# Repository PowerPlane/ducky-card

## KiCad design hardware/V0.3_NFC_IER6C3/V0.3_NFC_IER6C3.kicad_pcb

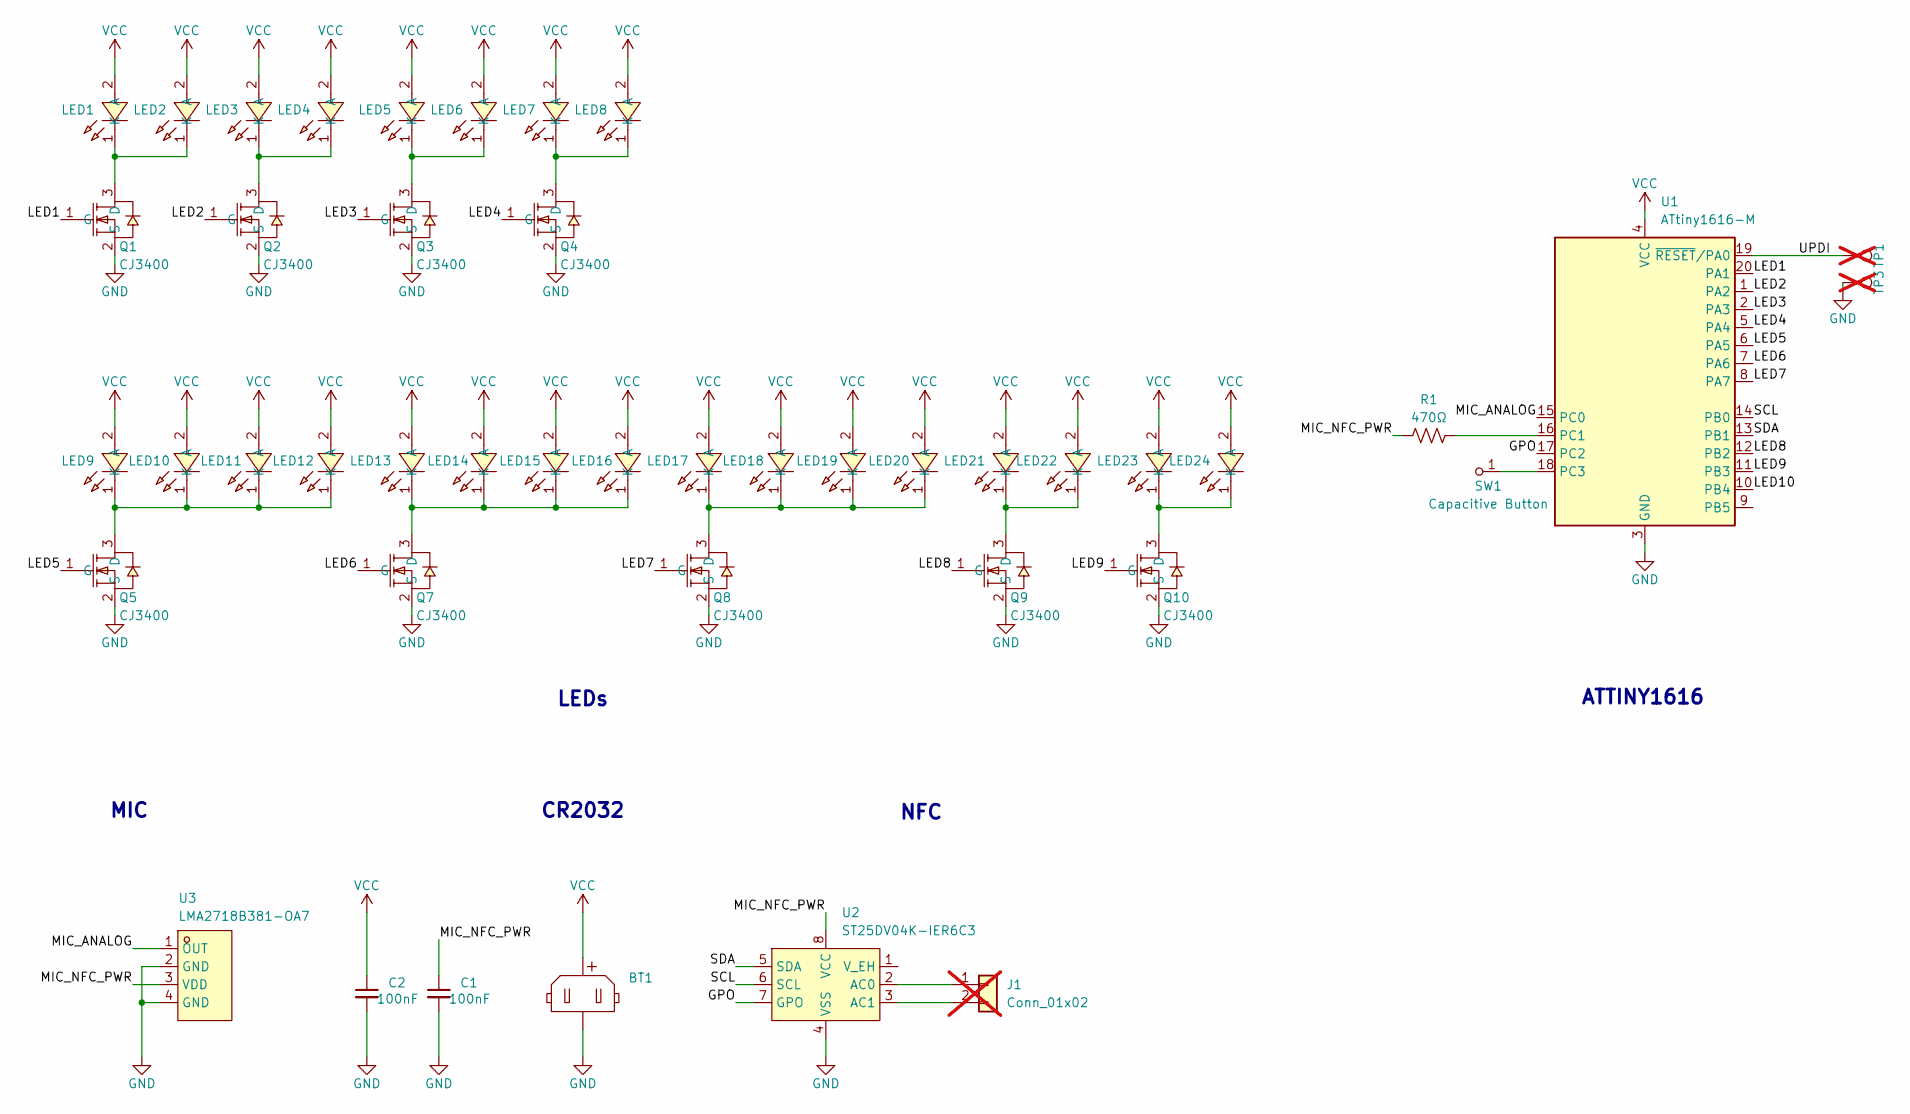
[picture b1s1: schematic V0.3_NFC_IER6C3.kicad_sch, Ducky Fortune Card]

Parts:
BT1: Battery-Holder_Coin-Cell_CR2032_Linx_BAT-HLD-001; BAT-SMD_MY-2032-08
C1, C2: 100nF; C_0805; Voltage 50V; Tolerance 100%; LCSC C28233
J1: Conn_01x02; NFC_Mini_Antenna_22x22_ST25DV04K; not fitted
LED1, LED2, LED3, LED4, LED5, LED6, LED7, LED8, LED9, LED10, LED11, LED12, LED13, LED14, LED15, LED16, LED17, LED18, LED19, LED20: XL-1606UYC; LED-SMD_L1.7-W1.1-RD_RED-SIDE; MPN XL-1606SURC; LCSC C965862
LED21, LED22: XL-1606UOC; LED-SMD_L1.7-W1.1-RD_RED-SIDE; MPN XL-1606SURC; LCSC C965861
LED23, LED24: XL-1606SURC; LED-SMD_L1.7-W1.1-RD_RED-SIDE; MPN XL-1606SURC; LCSC C965860
Q1, Q2, Q3, Q4, Q5, Q7, Q8, Q9, Q10: CJ3400; SOT23-3; MPN CJ3400; LCSC C19019
R1: 470Ω; R_0402; LCSC C25117
SW1: Capacitive Button; Ducky_Left_12mm_Overall
TP1, TP3: 1.0mm; DUCKY_ICON_2.54_Spacing; not fitted
U1: ATtiny1616-M; VQFN-20-1EP_3x3mm_P0.4mm_EP1.7x1.7mm; LCSC C507118
U2: ST25DV04K-IER6C3; DFN-8-1EP_3x2mm_P0.5mm_EP1.36x1.46mm; LCSC C2908287
U3: LMA2718B381-OA7; MIC-SMD_4P-L2.8-W1.9_LMA2718B381-OA7; MPN LMA2718B381-OA7; LCSC Part C5373222

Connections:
/GPO: U1.17 (PC2), U2.7 (GPO)
/LED1: Q1.1 (G), U1.20 (PA1)
/LED2: Q2.1 (G), U1.1 (PA2)
/LED3: Q3.1 (G), U1.2 (PA3)
/LED4: Q4.1 (G), U1.5 (PA4)
/LED5: Q5.1 (G), U1.6 (PA5)
/LED6: Q7.1 (G), U1.7 (PA6)
/LED7: Q8.1 (G), U1.8 (PA7)
/LED8: Q9.1 (G), U1.12 (PB2)
/LED9: Q10.1 (G), U1.11 (PB3)
/LED10: U1.10 (PB4)
/MIC_ANALOG: U1.15 (PC0), U3.1 (OUT)
/MIC_NFC_PWR: C1.1, R1.2, U2.8 (VCC), U3.3 (VDD)
/SCL: U1.14 (PB0), U2.6 (SCL)
/SDA: U1.13 (PB1), U2.5 (SDA)
/UPDI: TP1.1 (1_1), U1.19 (~RESET/PA0)
GND: BT1.2 (-), C1.2, C2.2, Q1.2 (S), Q2.2 (S), Q3.2 (S), Q4.2 (S), Q5.2 (S), Q7.2 (S), Q8.2 (S), Q9.2 (S), Q10.2 (S), TP3.1 (1_1), U1.3 (GND), U1.21 (GND), U2.4 (VSS), U3.2 (GND), U3.4 (GND)
unnamed: J1.1, U2.2 (AC0)
unnamed: J1.2, U2.3 (AC1)
unnamed: LED1.1 (K), LED2.1 (K), Q1.3 (D)
unnamed: LED3.1 (K), LED4.1 (K), Q2.3 (D)
unnamed: LED5.1 (K), LED6.1 (K), Q3.3 (D)
unnamed: LED7.1 (K), LED8.1 (K), Q4.3 (D)
unnamed: LED9.1 (K), LED10.1 (K), LED11.1 (K), LED12.1 (K), Q5.3 (D)
unnamed: LED13.1 (K), LED14.1 (K), LED15.1 (K), LED16.1 (K), Q7.3 (D)
unnamed: LED17.1 (K), LED18.1 (K), LED19.1 (K), LED20.1 (K), Q8.3 (D)
unnamed: LED21.1 (K), LED22.1 (K), Q9.3 (D)
unnamed: LED23.1 (K), LED24.1 (K), Q10.3 (D)
unnamed: SW1.1 (A_1), U1.18 (PC3)
unnamed: R1.1, U1.16 (PC1)
VCC: BT1.1 (+), C2.1, LED1.2 (A), LED2.2 (A), LED3.2 (A), LED4.2 (A), LED5.2 (A), LED6.2 (A), LED7.2 (A), LED8.2 (A), LED9.2 (A), LED10.2 (A), LED11.2 (A), LED12.2 (A), LED13.2 (A), LED14.2 (A), LED15.2 (A), LED16.2 (A), LED17.2 (A), LED18.2 (A), LED19.2 (A), LED20.2 (A), LED21.2 (A), LED22.2 (A), LED23.2 (A), LED24.2 (A), U1.4 (VCC)

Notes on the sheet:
NFC
LEDs
CR2032
ATTINY1616
MIC

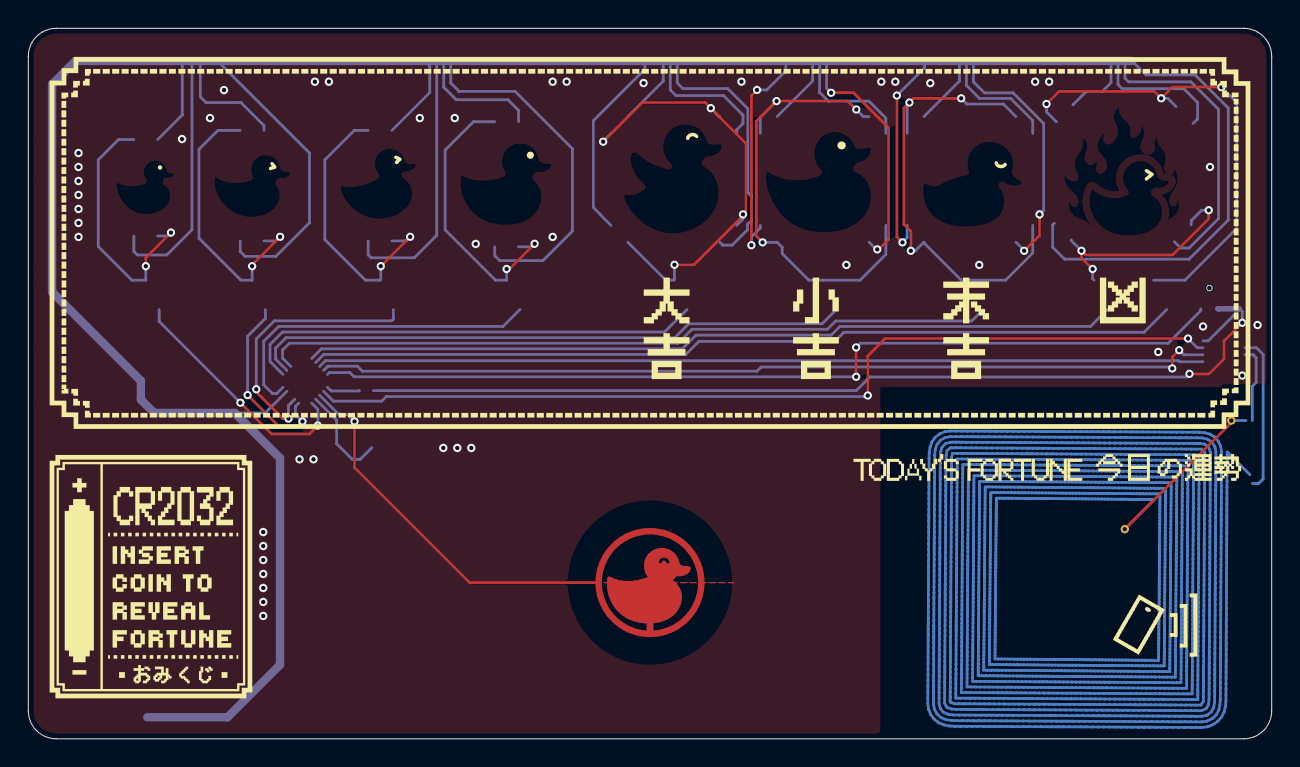
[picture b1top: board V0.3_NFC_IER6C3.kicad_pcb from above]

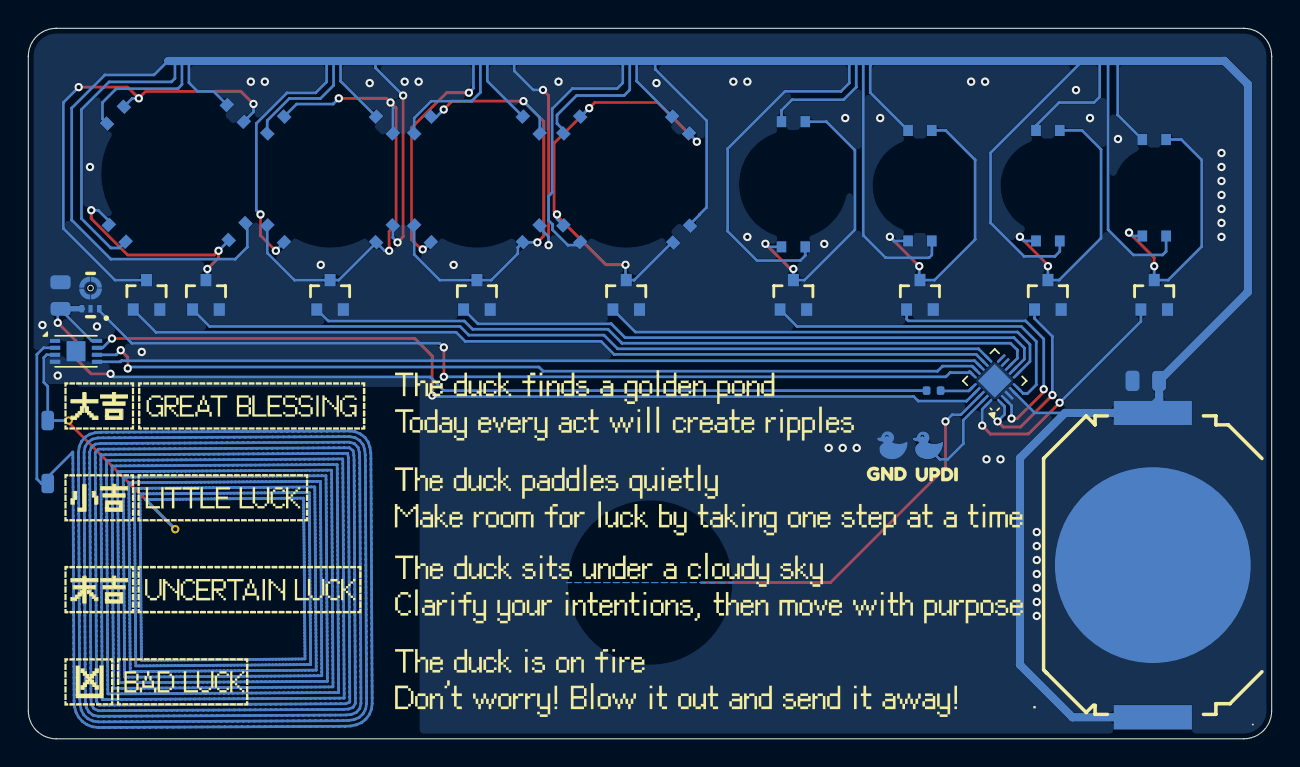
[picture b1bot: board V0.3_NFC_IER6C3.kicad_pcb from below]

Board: 2 copper layers, 88.9 x 50.8 mm, 46 parts (45 on the bottom side), 30 nets.

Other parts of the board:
kibuzzard-6A02DFFE: G***; kibuzzard-6A02DFFE
kibuzzard-6A02E019: G***; kibuzzard-6A02E019

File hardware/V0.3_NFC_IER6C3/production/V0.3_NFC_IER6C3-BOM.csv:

Designator,Footprint,Quantity,Value,LCSC Part #
BT1,BAT-SMD_MY-2032-08,1,Battery-Holder_Coin-Cell_CR2032_Linx_BAT-HLD-001,C964832
"C1, C2",C_0805,2,100nF,C28233
"LED1, LED10, LED11, LED12, LED13, LED14, LED15, LED16, LED17, LED18, LED19, LED2, LED20, LED3, LED4, LED5, LED6, LED7, LED8, LED9",LED-SMD_L1.7-W1.1-RD_RED-SIDE,20,XL-1606UYC,C965862
"LED21, LED22",LED-SMD_L1.7-W1.1-RD_RED-SIDE,2,XL-1606UOC,C965861
"LED23, LED24",LED-SMD_L1.7-W1.1-RD_RED-SIDE,2,XL-1606SURC,C965860
"Q1, Q10, Q2, Q3, Q4, Q5, Q7, Q8, Q9",SOT23-3,9,CJ3400,C19019
R1,R_0402,1,470Ω,C25117
U1,VQFN-20-1EP_3x3mm_P0.4mm_EP1.7x1.7mm,1,ATtiny1616-M,C507118
U2,DFN-8-1EP_3x2mm_P0.5mm_EP1.36x1.46mm,1,ST25DV04K-IER6C3,C2908287
U3,MIC-SMD_4P-L2.8-W1.9_LMA2718B381-OA7,1,LMA2718B381-OA7,C5373222
